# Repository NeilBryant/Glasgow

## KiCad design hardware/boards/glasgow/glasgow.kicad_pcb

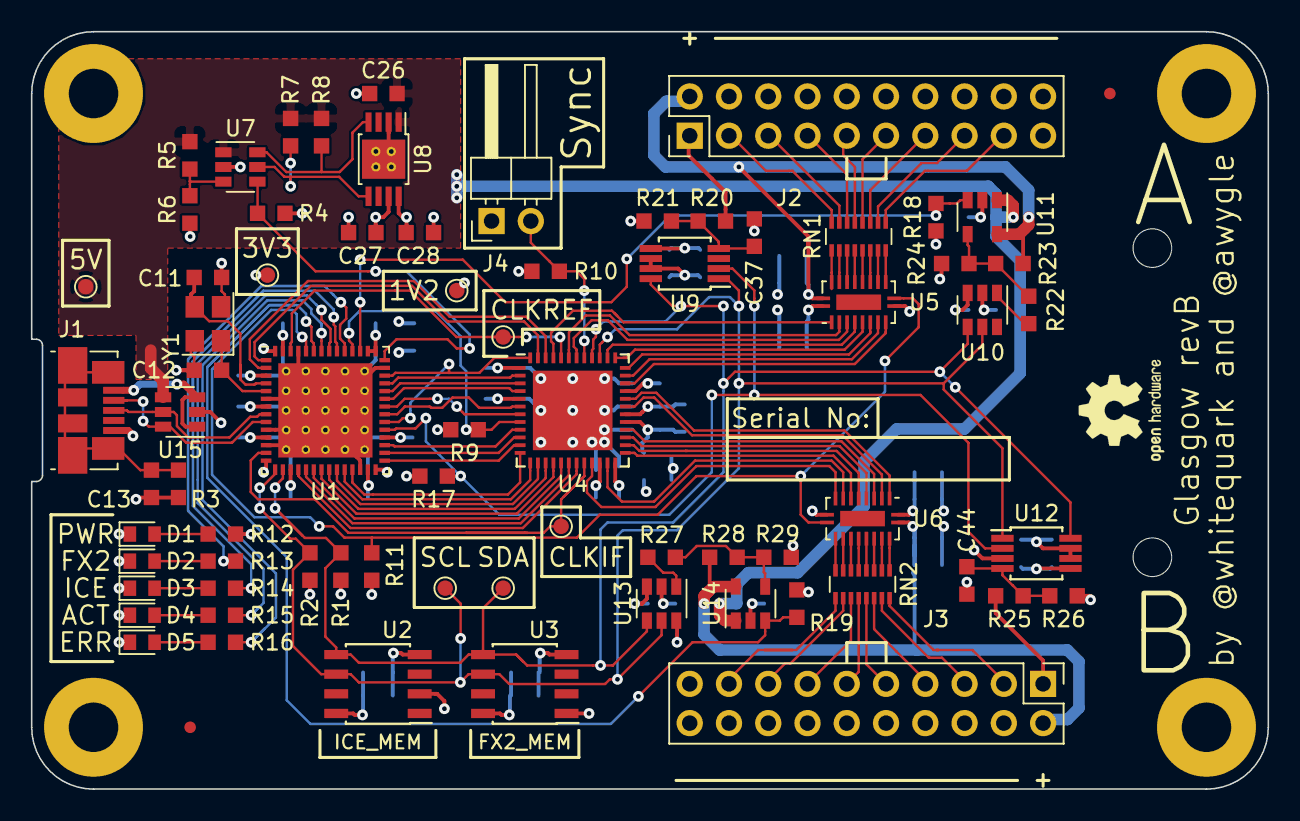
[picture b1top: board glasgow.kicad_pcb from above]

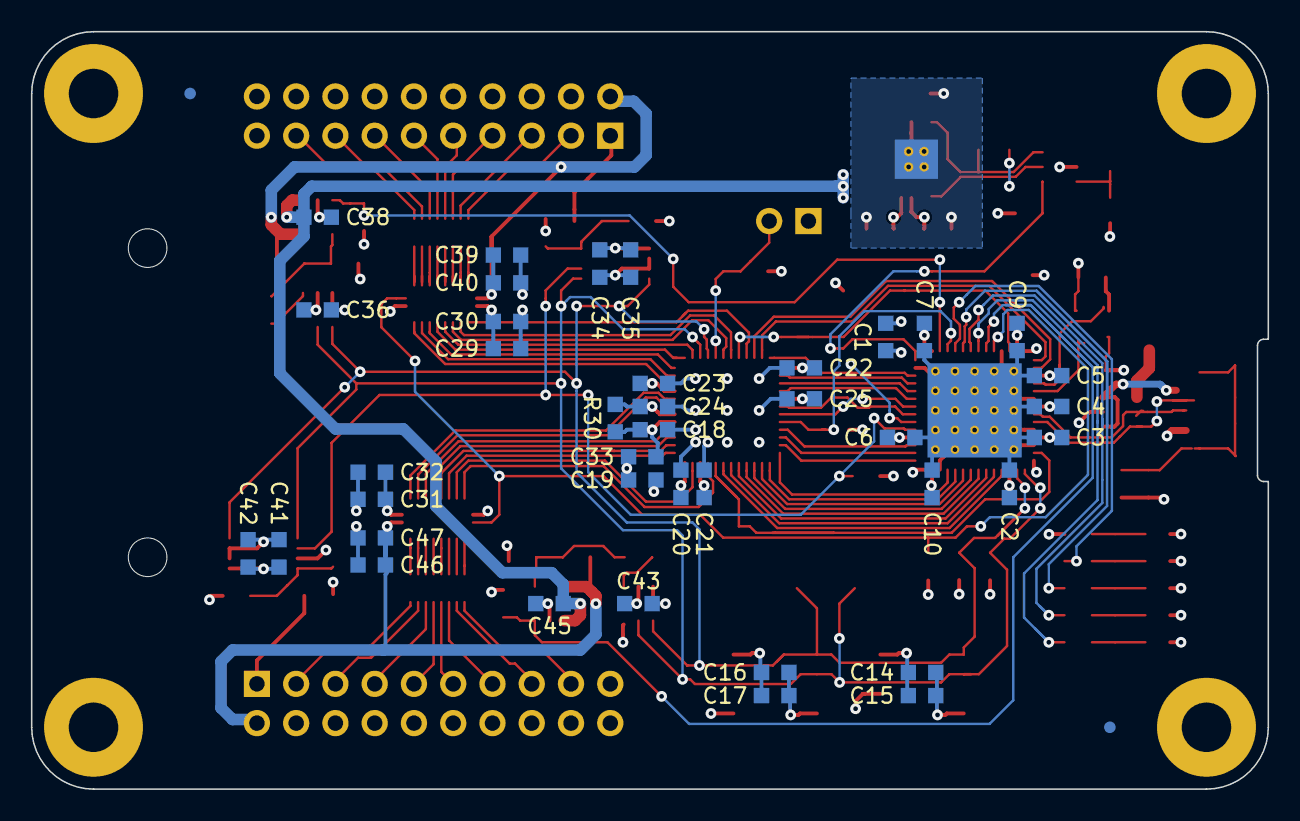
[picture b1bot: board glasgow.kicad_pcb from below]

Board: 4 copper layers, 80.0 x 49.0 mm, 120 parts (41 on the bottom side), 111 nets.

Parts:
C1, C14, C16, C18, C19, C26, C27, C28, C29, C31, C34, C39, C41, C46: 4u7; C_0603_1608Metric_Pad0.99x1.00mm_HandSolder
C2, C3, C4, C5, C6, C7, C9, C10, C13, C15, C17, C20, C21, C22, C23, C24, C25, C30, C32, C33, C35, C36, C38, C40, C42, C43, C45, C47: u1; C_0603_1608Metric_Pad0.99x1.00mm_HandSolder
C11, C12: 18p; C_0603_1608Metric_Pad0.99x1.00mm_HandSolder
C37, C44: 12n; C_0603_1608Metric_Pad0.99x1.00mm_HandSolder
D1, D2, D3: GRN; LED_0603_1608Metric_Pad0.82x1.00mm_HandSolder
D4: YEL; LED_0603_1608Metric_Pad0.82x1.00mm_HandSolder
D5: RED; LED_0603_1608Metric_Pad0.82x1.00mm_HandSolder
FID1, FID1#2, FID2, FID4: Fiducial_0.75mm_Dia_1.5mm_Outer
J1: USB_B_Micro; USB_Micro-B_Molex_47346-0001
J2, J3: Conn_02x10_Odd_Even; PinHeader_2x10_P2.54mm_Vertical
J4: Conn_01x02; PinHeader_1x02_P2.54mm_Horizontal
MK1, MK2, MK3, MK4: Mounting_Hole_PAD; MountingHole_3.2mm_M3_Pad
MK5, MK6: Mounting_Hole; MountingHole_2.5mm
R1, R2, R10, R12, R13, R14: 2k2; R_0603_1608Metric_Pad0.99x1.00mm_HandSolder
R3: 1M; R_0603_1608Metric_Pad0.99x1.00mm_HandSolder
R4, R6, R7, R8, R9, R11, R17, R18, R19: 100k; R_0603_1608Metric_Pad0.99x1.00mm_HandSolder
R5: 220k; R_0603_1608Metric_Pad0.99x1.00mm_HandSolder
R15: 390; R_0603_1608Metric_Pad0.99x1.00mm_HandSolder
R16: 604; R_0603_1608Metric_Pad0.99x1.00mm_HandSolder
R20, R21, R25, R26: 10k; R_0603_1608Metric_Pad0.99x1.00mm_HandSolder
R22, R27: 49k9; R_0603_1608Metric_Pad0.99x1.00mm_HandSolder
R23, R28: 59k; R_0603_1608Metric_Pad0.99x1.00mm_HandSolder
R24, R29: 24k3; R_0603_1608Metric_Pad0.99x1.00mm_HandSolder
R30: 100; R_0603_1608Metric_Pad0.99x1.00mm_HandSolder
RN1, RN2: R_Pack08; R_Array_Convex_8x0602
TP1: 5V; TestPoint_Pad_D1.0mm
TP2: 1V2; TestPoint_Pad_D1.0mm
TP3, TP7: 3V3; TestPoint_Pad_D1.0mm
TP4: SDA; TestPoint_Pad_D1.0mm
TP5: SCL; TestPoint_Pad_D1.0mm
TP6: CLKREF; TestPoint_Pad_D1.0mm
U1: CY7C68013A-56LTX; QFN-56-1EP_8x8mm_P0.5mm_EP6.1x6.1mm_ThermalVias
U2: CAT24M01W; SOIC-8_3.9x4.9mm_P1.27mm
U3: CAT24C256W; SOIC-8_3.9x4.9mm_P1.27mm
U4: ICE40UP5K-SG48ITR; QFN-48-1EP_7x7mm_P0.5mm_EP5.15x5.15mm
U5, U6: FXMA108BQX; WQFN-20-1EP_2.5x4.5mm_P0.5mm_EP1x2.9mm
U7: LM3880MF-1AF; SOT-23-6
U8: MIC5355-S4YMME; MSOP-8-1EP_3x3mm_P0.65mm_EP2.54x2.8mm_ThermalVias
U9, U12: ADC081C021CIMM; MSOP-8_3x3mm_P0.65mm
U10, U13: DAC081C081CIMK; SOT-23-6
U11, U14: TPS73101DBV; SOT-23-5
U15: TPD3S014; SOT-23-6
Y1: 24M; Crystal_SMD_3225-4pin_3.2x2.5mm

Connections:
+1V2: C24.1, C25.1, C27.1, R30.2, TP2.1, U4.5, U4.30, U8.7
+3V3: C1.1, C2.1, C3.1, C4.1, C5.1, C6.1, C7.1, C9.1, C10.1, C14.1, C15.1, C16.1, C17.1, C19.1, C20.1, C21.1, C22.1, C23.1, C28.1, C29.1, C30.1, C31.1, C32.1, C34.1, C35.1, C36.1, C41.1, C42.1, C43.1, R1.2, R2.2, R4.2, R10.2, R11.2, R12.1, R17.2, TP3.1, U1.3, U1.7, U1.11, U1.17, U1.27, U1.32, U1.43, U1.44, U1.55, U2.2, U2.8, U3.1, U3.8, U4.1, U4.22, U4.24, U4.33, U5.1, U6.1, U8.8, U9.5, U10.2, U12.5, U13.2
+5V: C26.1, C38.1, C45.1, R5.2, R7.2, R8.2, TP1.1, U7.1, U8.1, U11.1, U14.1, U15.4
/1V2EN: R8.1, U7.6, U8.4
/3V3EN: R7.1, U7.5, U8.5
/A0: U1.37, U4.4
/A1: U1.38, U4.3
/CLKIF: TP7.1, U1.13, U4.20
/CLKREF: TP6.1, U1.54, U4.44
/D0: U1.18, U4.19
/D1: U1.19, U4.18
/D2: U1.20, U4.17
/D3: U1.21, U4.16
/D4: U1.22, U4.15
/D5: U1.23, U4.14
/D6: U1.24, U4.13
/D7: U1.25, U4.12
/ENVA: R18.1, U1.45, U11.3
/ENVB: R19.1, U1.51, U14.3
/FLAGA: U1.29, U4.11
/FLAGB: U1.30, U4.10
/FLAGC: U1.31, U4.9
/FLAGD: U1.34, U1.40, U4.48
/FPGA_DONE: U1.36, U4.7
/IOBufferA/VFB: R22.2, R23.1, R24.2, U11.4
/IOBufferA/VIO: C39.1, C40.1, J2.2, R23.2, U5.20, U11.5
/IOBufferA/VSAMP: C37.1, R20.1, R21.2, U9.4
/IOBufferA/VSENSE: J2.1, R20.2
/IOBufferA/Y0: RN1.1, U5.19
/IOBufferA/Y1: RN1.2, U5.18
/IOBufferA/Y2: RN1.3, U5.17
/IOBufferA/Y3: RN1.4, U5.16
/IOBufferA/Y4: RN1.5, U5.15
/IOBufferA/Y5: RN1.6, U5.14
/IOBufferA/Y6: RN1.7, U5.13
/IOBufferA/Y7: RN1.8, U5.12
/IOBufferA/Z0: J2.3, RN1.16
/IOBufferA/Z1: J2.5, RN1.15
/IOBufferA/Z2: J2.7, RN1.14
/IOBufferA/Z3: J2.9, RN1.13
/IOBufferA/Z4: J2.11, RN1.12
/IOBufferA/Z5: J2.13, RN1.11
/IOBufferA/Z6: J2.15, RN1.10
/IOBufferA/Z7: J2.17, RN1.9
/IOBufferB/VFB: R27.2, R28.1, R29.2, U14.4
/IOBufferB/VIO: C46.1, C47.1, J3.2, R28.2, U6.20, U14.5
/IOBufferB/VSAMP: C44.1, R25.1, R26.2, U12.4
/IOBufferB/VSENSE: J3.1, R25.2
/IOBufferB/Y0: RN2.1, U6.19
/IOBufferB/Y1: RN2.2, U6.18
/IOBufferB/Y2: RN2.3, U6.17
/IOBufferB/Y3: RN2.4, U6.16
/IOBufferB/Y4: RN2.5, U6.15
/IOBufferB/Y5: RN2.6, U6.14
/IOBufferB/Y6: RN2.7, U6.13
/IOBufferB/Y7: RN2.8, U6.12
/IOBufferB/Z0: J3.3, RN2.16
/IOBufferB/Z1: J3.5, RN2.15
/IOBufferB/Z2: J3.7, RN2.14
/IOBufferB/Z3: J3.9, RN2.13
/IOBufferB/Z4: J3.11, RN2.12
/IOBufferB/Z5: J3.13, RN2.11
/IOBufferB/Z6: J3.15, RN2.10
/IOBufferB/Z7: J3.17, RN2.9
/LED_ACT: R15.1, U1.49
/LED_CY: R13.1, U1.47
/LED_ERR: R16.1, U1.50
/LED_FPGA: R14.1, U1.48
/OE: U1.35, U4.6
/PGOOD: R5.1, R6.2, U7.3
/PKTEND: U1.39, U4.2
/QA0: U4.45, U5.2
/QA1: U4.43, U5.3
/QA2: U4.42, U5.4
/QA3: U4.38, U5.5
/QA4: U4.37, U5.6
/QA5: U4.36, U5.7
/QA6: U4.35, U5.8
/QA7: U4.34, U5.9
/QB0: U4.32, U6.2
/QB1: U4.31, U6.3
/QB2: U4.28, U6.4
/QB3: U4.27, U6.5
/QB4: U4.26, U6.6
/QB5: U4.25, U6.7
/QB6: U4.23, U6.8
/QB7: U4.21, U6.9
/RD: U1.1, U4.47
/SCL: R2.1, TP5.1, U1.15, U2.6, U3.6, U4.39, U9.1, U10.5, U12.1, U13.5
/SDA: R1.1, TP4.1, U1.16, U2.5, U3.5, U4.40, U9.8, U10.4, U12.8, U13.4
/SHLD: C13.1, J1.6, R3.1
/USB_N: J1.2, U1.9, U15.6
/USB_P: J1.3, U1.8, U15.5
/VCCPLL: C18.1, C33.1, R30.1, U4.29
/VUSB: J1.1, U15.1, U15.3
/WR: U1.2, U4.46
/XTALIN: C12.1, U1.5, Y1.1
/XTALOUT: C11.1, U1.4, Y1.3
/~ALERT: R17.1, U1.33, U9.2, U12.2
/~CY_RESET: R4.1, U1.42, U7.4
/~FPGA_RESET: R9.2, U1.46, U4.8
/~OEQ: R11.1, U1.52, U5.11, U6.11
/~SYNC: J4.2, R10.1, U4.41
GND: C1.2, C2.2, C3.2, C4.2, C5.2, C6.2, C7.2, C9.2, C10.2, C11.2, C12.2, C13.2, C14.2, C15.2, C16.2, C17.2, C18.2, C19.2, C20.2, C21.2, C22.2, C23.2, C24.2, C25.2, C26.2, C27.2, C28.2, C29.2, C30.2, C31.2, C32.2, C33.2, C34.2, C35.2, C36.2, C37.2, C38.2, C39.2, C40.2, C41.2, C42.2, C43.2, C44.2, C45.2, C46.2, C47.2, D1.1, D2.1, D3.1, D4.1, D5.1, J1.5, J2.4, J2.6, J2.8, J2.10, J2.12, J2.14, J2.16, J2.18, J2.20, J3.4, J3.6, J3.8, J3.10, J3.12, J3.14, J3.16, J3.18, J3.20, J4.1, MK1.1, MK2.1, MK3.1, MK4.1, R3.2, R6.1, R9.1, R18.2, R19.2, R21.1, R24.1, R26.1, R29.1, U1.6, U1.10, U1.12, U1.14, U1.26, U1.28, U1.41, U1.53, U1.56, U1.57, U2.4, U3.4, U4.49, U5.10, U6.10, U7.2, U8.2, U8.9, U9.6, U9.7, U10.3, U11.2, U12.3, U12.6, U12.7, U13.3, U13.6, U14.2, U15.2, Y1.2, Y1.4
unnamed: D1.2, R12.2
unnamed: D2.2, R13.2
unnamed: D3.2, R14.2
unnamed: D4.2, R15.2
unnamed: D5.2, R16.2
unnamed: R22.1, U10.1
unnamed: R27.1, U13.1

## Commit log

2018-05-23 Add USB protection IC.
